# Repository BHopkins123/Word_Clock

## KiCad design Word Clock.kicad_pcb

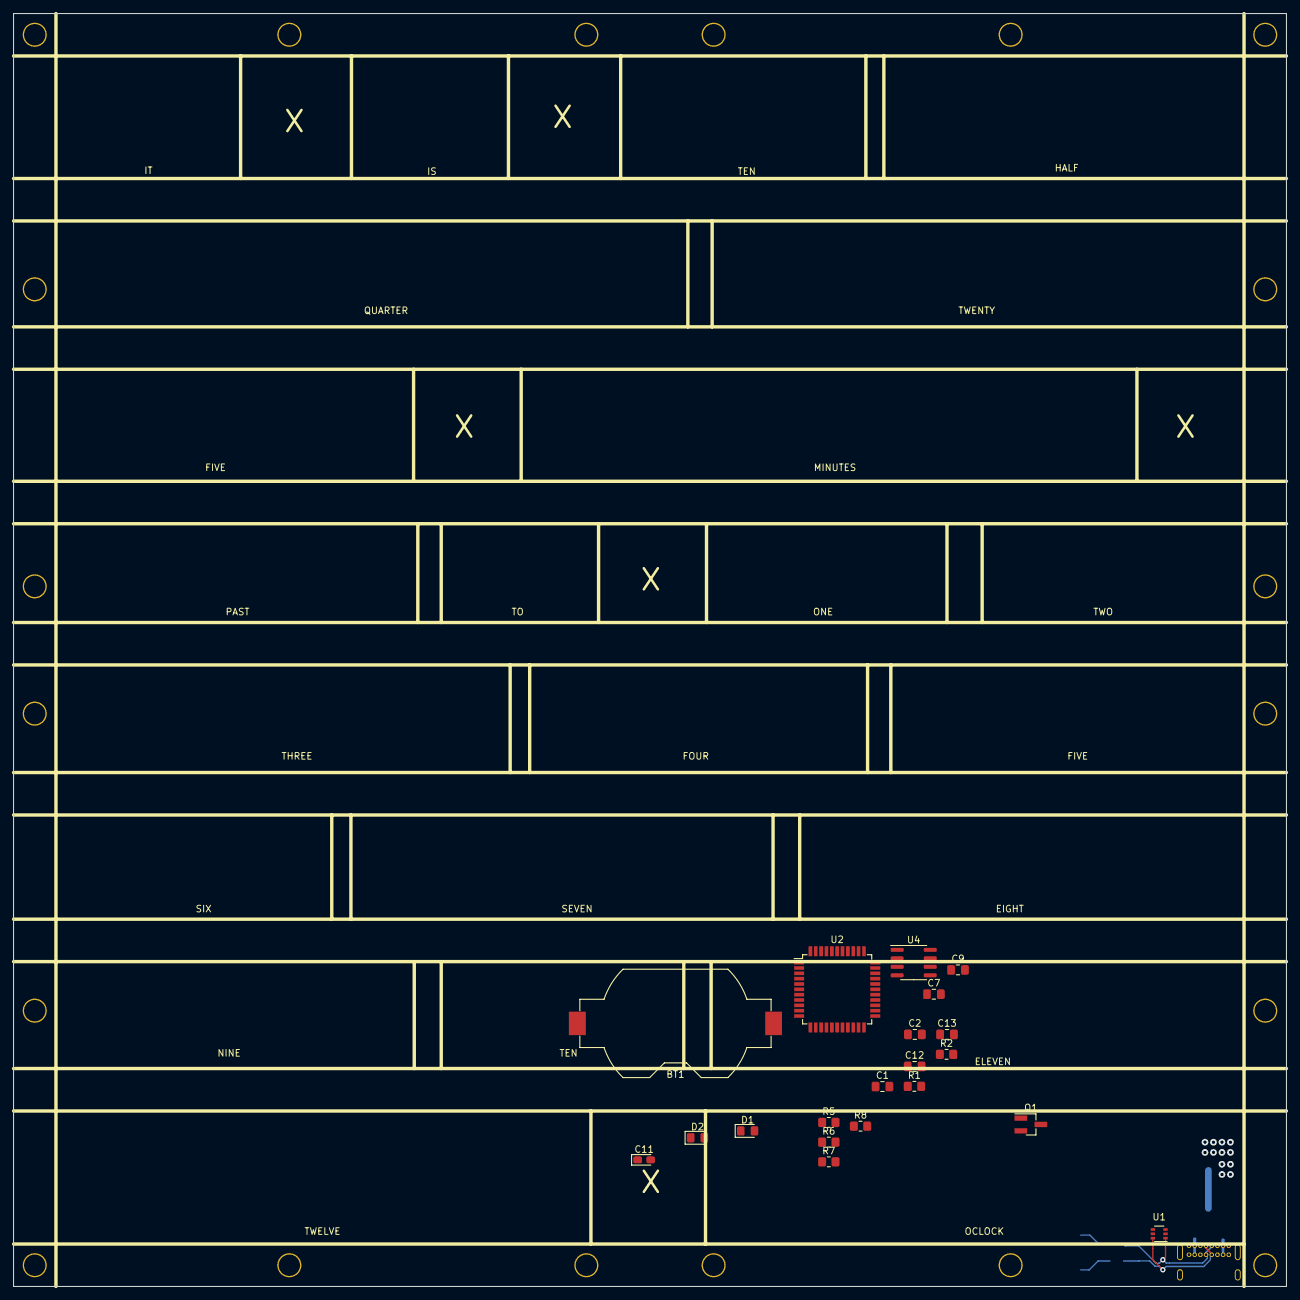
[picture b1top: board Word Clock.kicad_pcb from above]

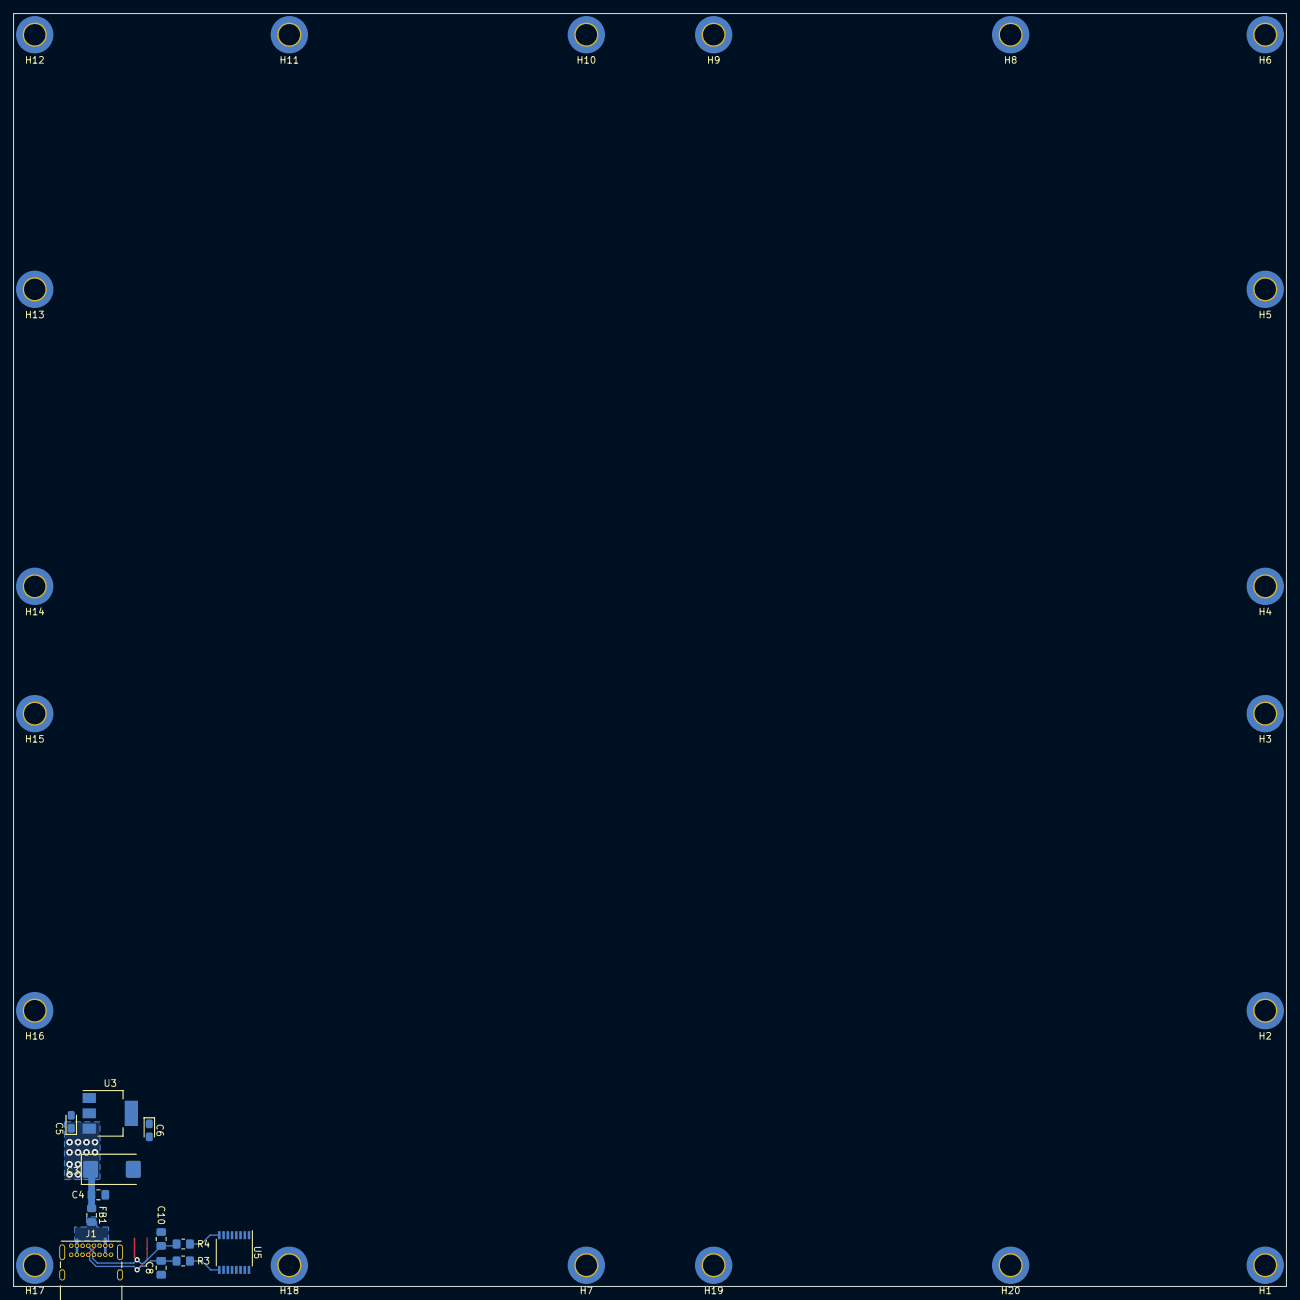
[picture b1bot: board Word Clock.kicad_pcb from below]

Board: 4 copper layers, 190.5 x 190.5 mm, 52 parts (32 on the bottom side), 18 nets.

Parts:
BT1: Battery_Cell; BatteryHolder_Keystone_1058_1x2032
C1, C2, C7, C9, C12: 0.1u; C_0805_2012Metric_Pad1.18x1.45mm_HandSolder
C3: 100µ; CP_EIA-7343-20_Kemet-V_Pad2.25x2.55mm_HandSolder
C4: 10n; C_0805_2012Metric_Pad1.18x1.45mm_HandSolder
C5, C6: 10µ; CP_EIA-2012-15_AVX-P_Pad1.30x1.05mm_HandSolder
C8, C10: 47pF; C_0805_2012Metric_Pad1.18x1.45mm_HandSolder
C11: 4.7µ; CP_EIA-2012-15_AVX-P_Pad1.30x1.05mm_HandSolder
C13: 1u; C_0805_2012Metric_Pad1.18x1.45mm_HandSolder
D1, D2: LED; LED_0805_2012Metric_Pad1.15x1.40mm_HandSolder
FB1: Ferrite_Bead_Small; L_0805_2012Metric_Pad1.15x1.40mm_HandSolder
H1, H2, H3, H4, H5, H6, H7, H8, H9, H10, H11, H12, H13, H14, H15, H16, H17, H18, H19, H20: MountingHole; MountingHole_3.2mm_M3_DIN965_Pad_TopOnly
J1: USB_C_Receptacle_USB2.0; USB_C_Receptacle_GCT_USB4085
Q1: Q_NMOS_GSD; SOT-23_Handsoldering
R1, R2, R5, R6: 10k; R_0805_2012Metric_Pad1.20x1.40mm_HandSolder
R3, R4: 27R; R_0805_2012Metric_Pad1.20x1.40mm_HandSolder
R7, R8: 270R; R_0805_2012Metric_Pad1.20x1.40mm_HandSolder
U1: NUP2202; SOT-363_SC-70-6
U2: PIC18LF46K80-IPT; TQFP-44_10x10mm_P0.8mm
U3: LM1117-3.3; SOT-223-3_TabPin2
U4: DS3231MZ; SOIC-8_3.9x4.9mm_P1.27mm
U5: FT230XS; SSOP-16_3.9x4.9mm_P0.635mm

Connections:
+3V3: C1.1, C2.1, C6.1, C12.1, C13.1, R1.1, R2.1, U2.7, U2.28, U3.2, U4.2
+5V: C3.1, C4.1, C5.1, C9.1, C11.1, FB1.1, U1.5, U3.3, U5.12
+BATT: BT1.1, U4.6
/PowerMicroRTCandComm/DN: C8.1, J1.7B7, J1.A7, R3.1, U1.6
/PowerMicroRTCandComm/DP: C10.1, J1.A6, J1.B6, R4.1, U1.1
/PowerMicroRTCandComm/FT3V3: C7.1, R5.1, R6.1, R7.1, R8.1, U5.3, U5.10, U5.11
/PowerMicroRTCandComm/SCL: R2.2, U2.37, U4.8
/PowerMicroRTCandComm/SDA: R1.2, U2.42, U4.7
/PowerMicroRTCandComm/UART_RX: R5.2, U2.1, U5.4
/PowerMicroRTCandComm/UART_TX: R6.2, U2.44, U5.1
GND: BT1.2, C1.2, C2.2, C3.2, C4.2, C5.2, C6.2, C7.2, C8.2, C9.2, C10.2, C11.2, C12.2, C13.2, J1.A1, J1.A12, J1.B1, J1.B12, J1.S1, U1.2, U2.6, U2.29, U3.1, U4.5, U5.5, U5.13
unnamed: D1.1, U5.14
unnamed: D1.2, R7.2
unnamed: D2.1, U5.7
unnamed: D2.2, R8.2
unnamed: FB1.2, J1.A4, J1.A9, J1.B4, J1.B9
unnamed: R3.2, U5.9
unnamed: R4.2, U5.8

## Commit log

2021-02-17 Initial commit. Schematic is mostly done, but needs cleaning up. Board layout has been started but no real progress has been made on it .
2021-03-02 Added lines in the silk so the LEDs can be placed accurately.
2021-03-02 Starting some prelim layout. Perhaps I should finish my schematics and place all my parts first.... But what do I know?
2021-03-03 Schematic is almost finished. The MCLR circuit needs completing, the hour/minute inputs also need their input protection.
    After that, I might have one of the guys from work review it. But, who knows.
